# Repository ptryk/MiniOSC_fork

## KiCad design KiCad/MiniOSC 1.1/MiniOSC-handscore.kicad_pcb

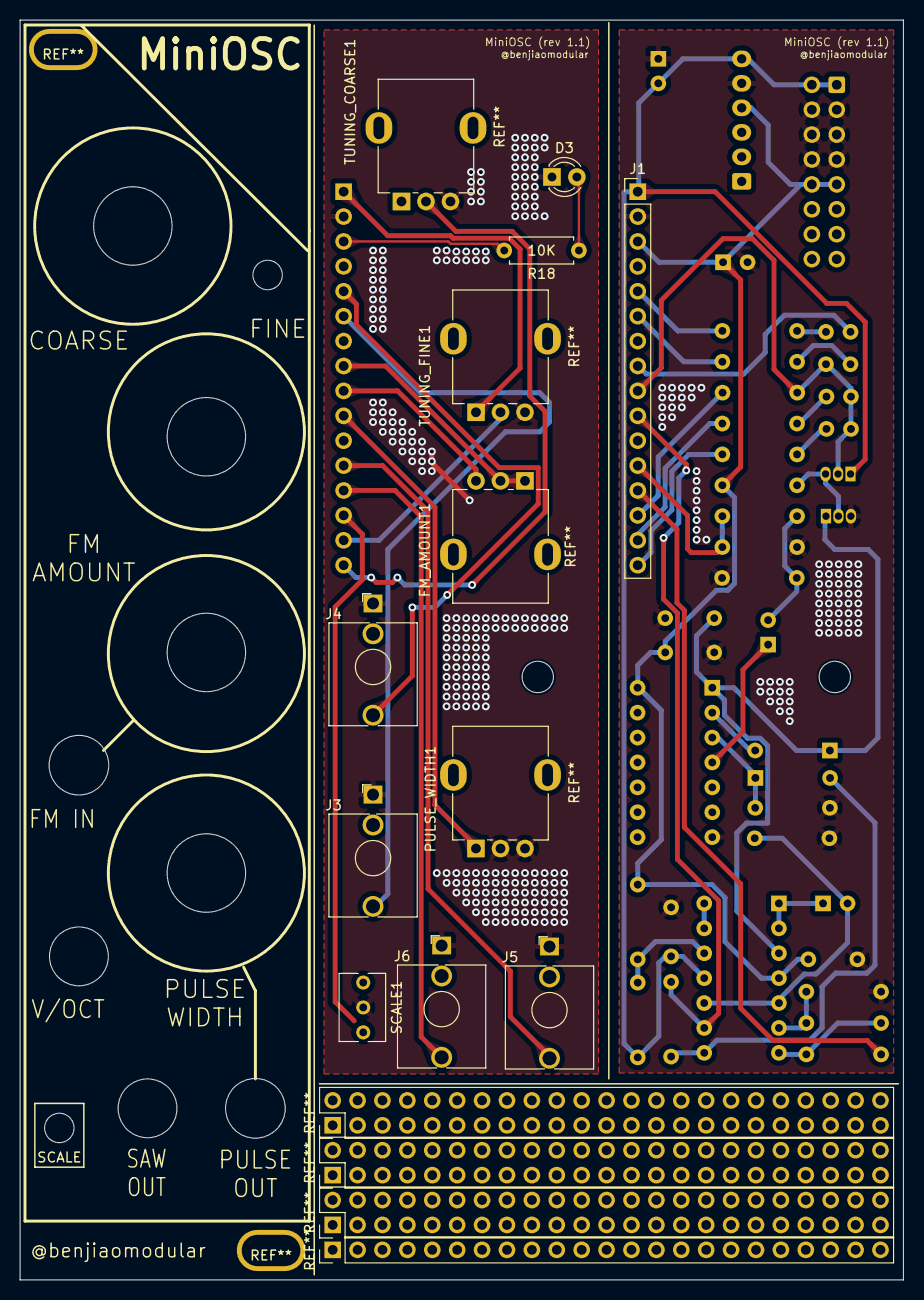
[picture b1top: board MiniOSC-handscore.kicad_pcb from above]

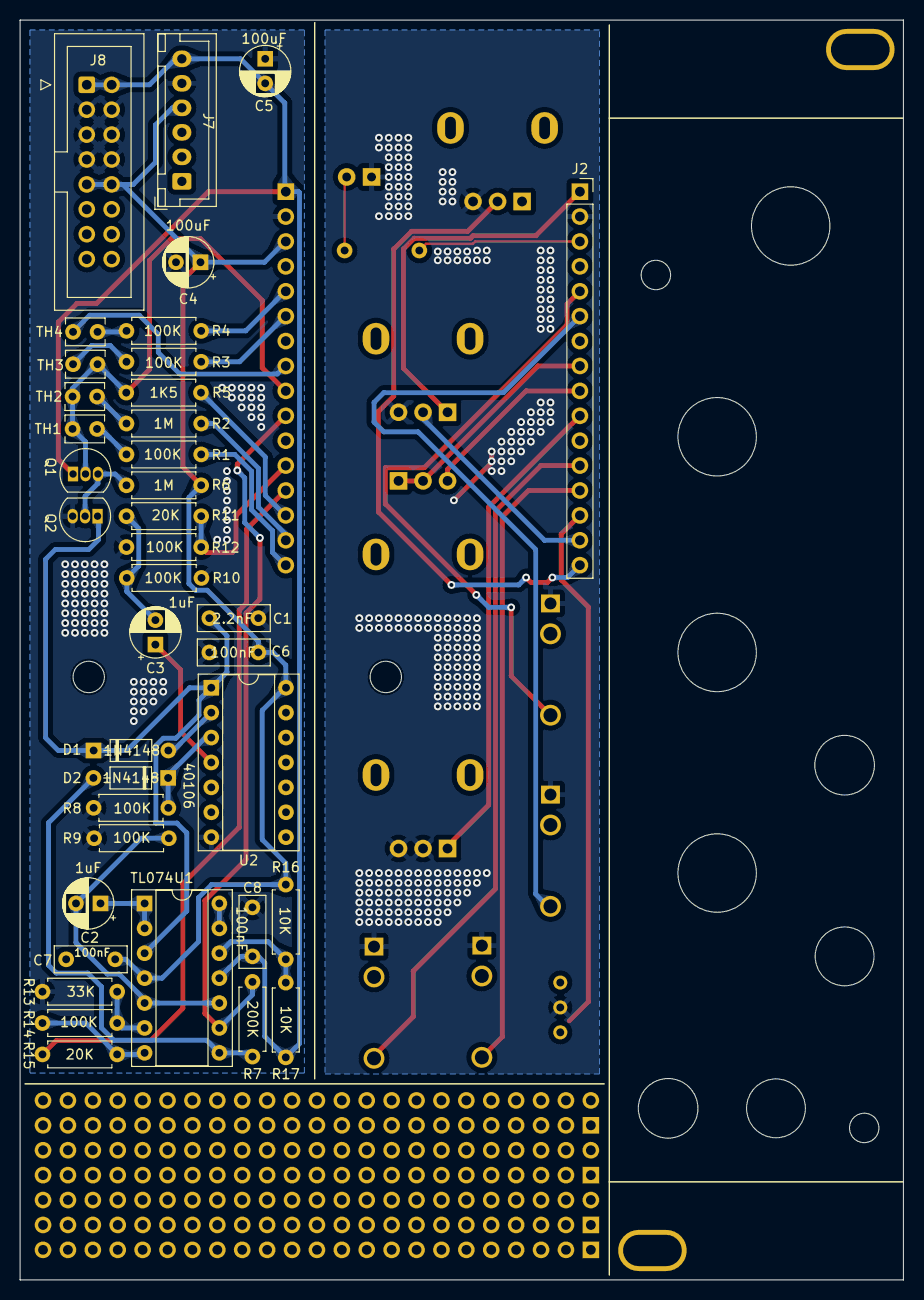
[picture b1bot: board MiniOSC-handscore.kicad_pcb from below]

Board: 2 copper layers, 90.1 x 128.5 mm, 50 parts (38 on the bottom side), 47 nets.

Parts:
C1: 2.2nF; C_Rect_L7.2mm_W2.5mm_P5.00mm_FKS2_FKP2_MKS2_MKP2
C2, C3: 1uF; CP_Radial_D5.0mm_P2.50mm
C4, C5: 100uF; CP_Radial_D5.0mm_P2.50mm
C6, C7, C8: 100nF; C_Rect_L7.2mm_W2.5mm_P5.00mm_FKS2_FKP2_MKS2_MKP2
D1, D2: 1N4148; D_DO-35_SOD27_P7.62mm_Horizontal
D3: LED; LED_D3.0mm
FM_AMOUNT1: 1M; Potentiometer_RV09
J1: Conn_01x16_Female; PinHeader_1x16_P2.54mm_Vertical
J2: Conn_01x16_Male; PinSocket_1x16_P2.54mm_Vertical
J3: V_OCT_IN; Jack_3.5mm_QingPu_WQP-PJ398SM_Vertical_CircularHoles
J4: FM_IN; Jack_3.5mm_QingPu_WQP-PJ398SM_Vertical_CircularHoles
J5: PULSE_OUT; Jack_3.5mm_QingPu_WQP-PJ398SM_Vertical_CircularHoles
J6: SAW_OUT; Jack_3.5mm_QingPu_WQP-PJ398SM_Vertical_CircularHoles
J7: JST_BUS; JST_XH_B6B-XH-A_1x06_P2.50mm_Vertical
J8: IDC_BUS; IDC-Header_2x08_P2.54mm_Vertical
PULSE_WIDTH1: 100K; Potentiometer_RV09
Q1: BC558; TO-92_Inline
Q2: BC548; TO-92_Inline
R1, R3, R4, R8, R9, R10, R12, R14: 100K; R_Axial_DIN0207_L6.3mm_D2.5mm_P7.62mm_Horizontal
R2, R6: 1M; R_Axial_DIN0207_L6.3mm_D2.5mm_P7.62mm_Horizontal
R5: 1K5; R_Axial_DIN0207_L6.3mm_D2.5mm_P7.62mm_Horizontal
R7: 200K; R_Axial_DIN0207_L6.3mm_D2.5mm_P7.62mm_Horizontal
R11, R15: 20K; R_Axial_DIN0207_L6.3mm_D2.5mm_P7.62mm_Horizontal
R13: 33K; R_Axial_DIN0207_L6.3mm_D2.5mm_P7.62mm_Horizontal
R16, R17, R18: 10K; R_Axial_DIN0207_L6.3mm_D2.5mm_P7.62mm_Horizontal
SCALE1: 1K; Potentiometer_Bourns_3266Y_Vertical
TH1, TH2, TH3, TH4: 10K NTC; C_Disc_D3.8mm_W2.6mm_P2.50mm
TUNING_COARSE1: 100K; Potentiometer_RV09
TUNING_FINE1: 100K; Potentiometer_RV09
U1: TL074; DIP-14_W7.62mm_Socket
U2: 40106; DIP-14_W7.62mm_Socket

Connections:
+12V: C4.1, C6.1, C7.1, J1.3, J7.4, J8.9, J8.10, R6.2, R16.2, U1.4, U2.14
-12V: C5.2, C8.2, J1.1, J7.6, J8.1, J8.2, Q1.1, R17.1, U1.11
/FrontPanel/FP_12V_POS: J2.3, R18.2
/FrontPanel/FP_COARSE: J2.16, TUNING_COARSE1.2
/FrontPanel/FP_FINE: J2.15, TUNING_FINE1.2
/FrontPanel/FP_FM_AMT_P2: FM_AMOUNT1.1, FM_AMOUNT1.2, J2.8
/FrontPanel/FP_FM_AMT_P3: FM_AMOUNT1.3, J2.9
/FrontPanel/FP_FM_IN: J2.5, J4.T
/FrontPanel/FP_PULSE_OUT: J2.12, J5.T
/FrontPanel/FP_PULSE_WIDTH: J2.10, PULSE_WIDTH1.1
/FrontPanel/FP_SAW_OUT: J2.13, J6.T
/FrontPanel/FP_SCALE: J2.14, SCALE1.1
/FrontPanel/FP_V_OCT_IN: J2.6, J3.T
Earth: C1.2, C4.2, C5.1, C6.2, C7.2, C8.1, J1.2, J7.5, J8.3, J8.4, J8.5, J8.6, J8.7, J8.8, Q2.3, R8.1, R9.1, R10.1, R12.1, R13.2, U2.7
FM_AMT_P2: J1.8, TH4.1
FM_AMT_P3: J1.9, Q1.2, R5.2, TH1.1, TH2.1, TH3.1
FP_12V_NEG: J2.1, TUNING_COARSE1.1, TUNING_FINE1.1
GND1: D3.1, J2.2, J3.S, J4.S, J5.S, J6.S, PULSE_WIDTH1.2, PULSE_WIDTH1.3, SCALE1.2, TUNING_COARSE1.3, TUNING_FINE1.3
unnamed: C1.1, D1.1, Q2.1, U1.3, U2.1
unnamed: C2.1, U1.1, U1.2
unnamed: C2.2, R9.2, U1.5, U1.10
unnamed: C3.1, U2.4
unnamed: C3.2, R10.2, R11.1
unnamed: D1.2, U2.2
unnamed: D2.1, R8.2, U2.3
unnamed: D2.2, R7.2, U1.8
unnamed: D3.2, R18.1
unnamed: J1.5, R4.2
unnamed: J1.6, R3.2
unnamed: J1.15, R2.2
unnamed: J1.16, R1.2
unnamed: J8.11, J8.12
unnamed: J8.13, J8.14
unnamed: J8.15, J8.16
unnamed: Q1.3, Q2.2, R6.1
unnamed: R1.1, TH1.2
unnamed: R2.1, TH2.2
unnamed: R3.1, TH3.2
unnamed: R4.1, TH4.2
unnamed: R13.1, R14.1, U1.6
unnamed: R14.2, R15.1, U1.7
unnamed: R16.1, R17.2, U1.12
unnamed: U1.13, U1.14
PULSE_OUT: J1.12, R11.2, R12.2
PULSE_WIDTH: J1.10, R7.1, U1.9
SAW_OUT: J1.13, R15.2
SCALE: J1.14, R5.1

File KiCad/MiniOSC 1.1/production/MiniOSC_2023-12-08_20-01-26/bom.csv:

Designator,Footprint,Quantity,Value,LCSC Part #
C1,C_Rect_L7.2mm_W2.5mm_P5.00mm_FKS2_FKP2_MKS2_MKP2,1,2.2nF,
"C2, C3",CP_Radial_D5.0mm_P2.50mm,2,1uF,
"C4, C5",CP_Radial_D5.0mm_P2.50mm,2,100uF,
"C6, C7, C8",C_Rect_L7.2mm_W2.5mm_P5.00mm_FKS2_FKP2_MKS2_MKP2,3,100nF,
"D1, D2",D_DO-35_SOD27_P7.62mm_Horizontal,2,1N4148,
D3,LED_D3.0mm,1,LED,
FM_AMOUNT1,Potentiometer_RV09,1,1M,
J1,PinHeader_1x16_P2.54mm_Vertical,1,Conn_01x16_Female,
J2,PinSocket_1x16_P2.54mm_Vertical,1,Conn_01x16_Male,
J3,Jack_3.5mm_QingPu_WQP-PJ398SM_Vertical_CircularHoles,1,V_OCT_IN,
J4,Jack_3.5mm_QingPu_WQP-PJ398SM_Vertical_CircularHoles,1,FM_IN,
J5,Jack_3.5mm_QingPu_WQP-PJ398SM_Vertical_CircularHoles,1,PULSE_OUT,
J6,Jack_3.5mm_QingPu_WQP-PJ398SM_Vertical_CircularHoles,1,SAW_OUT,
J7,JST_XH_B6B-XH-A_1x06_P2.50mm_Vertical,1,JST_BUS,
J8,IDC-Header_2x08_P2.54mm_Vertical,1,IDC_BUS,
"PULSE_WIDTH1, TUNING_COARSE1, TUNING_FINE1",Potentiometer_RV09,3,100K,
Q1,TO-92_Inline,1,BC558,
Q2,TO-92_Inline,1,BC548,
"R1, R10, R12, R14, R3, R4, R8, R9",R_Axial_DIN0207_L6.3mm_D2.5mm_P7.62mm_Horizontal,8,100K,
"R11, R15",R_Axial_DIN0207_L6.3mm_D2.5mm_P7.62mm_Horizontal,2,20K,
R13,R_Axial_DIN0207_L6.3mm_D2.5mm_P7.62mm_Horizontal,1,33K,
"R16, R17, R18",R_Axial_DIN0207_L6.3mm_D2.5mm_P7.62mm_Horizontal,3,10K,
"R2, R6",R_Axial_DIN0207_L6.3mm_D2.5mm_P7.62mm_Horizontal,2,1M,
R5,R_Axial_DIN0207_L6.3mm_D2.5mm_P7.62mm_Horizontal,1,1K5,
R7,R_Axial_DIN0207_L6.3mm_D2.5mm_P7.62mm_Horizontal,1,200K,
SCALE1,Potentiometer_Bourns_3266Y_Vertical,1,1K,
"TH1, TH2, TH3, TH4",C_Disc_D3.8mm_W2.6mm_P2.50mm,4,10K NTC,
U1,DIP-14_W7.62mm_Socket,1,TL074,
U2,DIP-14_W7.62mm_Socket,1,40106,
"mouse-bite-2mm-slot_7, mouse-bite-2mm-slot_6, mouse-bite-2mm-slot_5, mouse-bite-2mm-slot_4, mouse-bite-2mm-slot_3, mouse-bite-2mm-slot_2, mouse-bite-2mm-slot",mouse-bite-2mm-slot,7,VAL**,

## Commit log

2023-12-08 some clean up v1.1 combined boards version changes r14 silkscreen switched + misc silkscreen fixes turned on teardrops output gerbers ouput bom
    then created handscore version - low cost
    adjusted routing to keep traces further from scored / break edges
    included teardrops
    then ouput gerbeeres + bom +
2023-12-09 now with gerber zips! for v1.1 and 1.1 handscore!
2023-12-11 some cleanup of directories :)
2023-12-20 fixing traces on fine tuning 1.1 and 1.1 handscore
